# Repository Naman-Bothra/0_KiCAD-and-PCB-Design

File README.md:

# 0_KiCAD-and-PCB-Design
# Simple LED Driver Circuit

A foundational, low-power hardware design featuring a single-cell battery source, a current-limiting resistor, and a Light Emitting Diode (LED). This project serves as a clean baseline for schematic capture, electrical rule checking (ERC), custom footprint assignment, and manufacturing output generation using KiCad.

---

##  Project Overview

The objective of this project is to implement a robust, reliable, and mathematically sound LED indicator loop. LEDs are non-linear components with negligible internal resistance once their forward voltage threshold is crossed. To prevent over-current conditions and immediate component failure, this circuit incorporates a precisely calculated series resistor acting as a dedicated current limiter.

### Key Specifications
* **Supply Voltage ($V_{CC}$):** 3.0V DC (Optimized for standard CR2032 or dual AA/AAA battery configurations)
* **Target Forward Current ($I_f$):** ~10mA to 15mA (Balances ideal brightness with battery longevity)
* **Form Factor:** Minimalist PCB, routing single-sided or dual-layer copper tracks.

---

## 📊 Schematic & Circuit Design

The circuit is designed entirely within the **KiCad Schematic Editor**. The architecture utilizes explicit power distribution nets to decouple the power generation node from the functional loop.

### Component Breakdown
* **BT101 (Battery_Cell):** Direct current (DC) source providing system potential.
* **R101 (R_US):** Current-limiting resistor configured using the US-style schematic symbol.
* **D101 (LED):** Standard semiconductor diode indicator.
* **PWR_FLAG:** KiCad utility power flags appended to the `VCC` and `GND` nets to explicitly declare power-generating pins and successfully satisfy Electrical Rules Check (ERC) compilation.

### The Physics (Ohm's Law Calculation)
To ensure optimal current regulation, the resistor value was derived using the standard load equation:

$$R = \frac{V_{CC} - V_f}{I_f}$$

*Where $V_f$ represents the forward voltage drop characteristic of the selected LED substrate (typically 1.8V to 2.1V for standard red/green indicators).*

---

## 🎨 PCB Layout & Manufacturing Best Practices

The physical implementation of the layout adheres strictly to industry-standard DFM (Design for Manufacturability) guidelines:

---

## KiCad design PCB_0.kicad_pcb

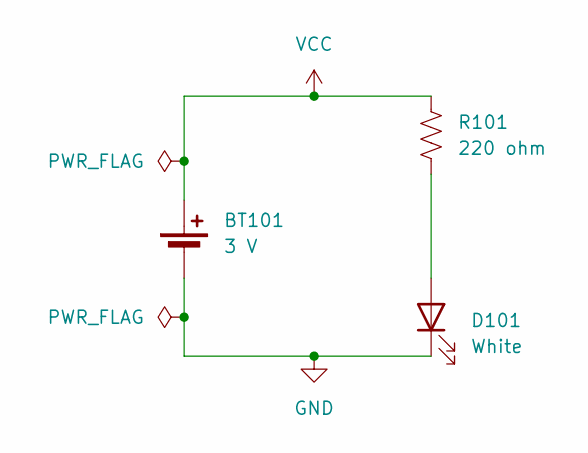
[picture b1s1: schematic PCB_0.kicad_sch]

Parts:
BT101: 3 V; BatteryHolder_Keystone_500
D101: White; LED_D3.0mm_Horizontal_O1.27mm_Z2.0mm_Clear
R101: 220 ohm; R_Axial_DIN0207_L6.3mm_D2.5mm_P2.54mm_Vertical

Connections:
GND: BT101.2 (-), D101.1 (K)
unnamed: D101.2 (A), R101.2
VCC: BT101.1 (+), R101.1

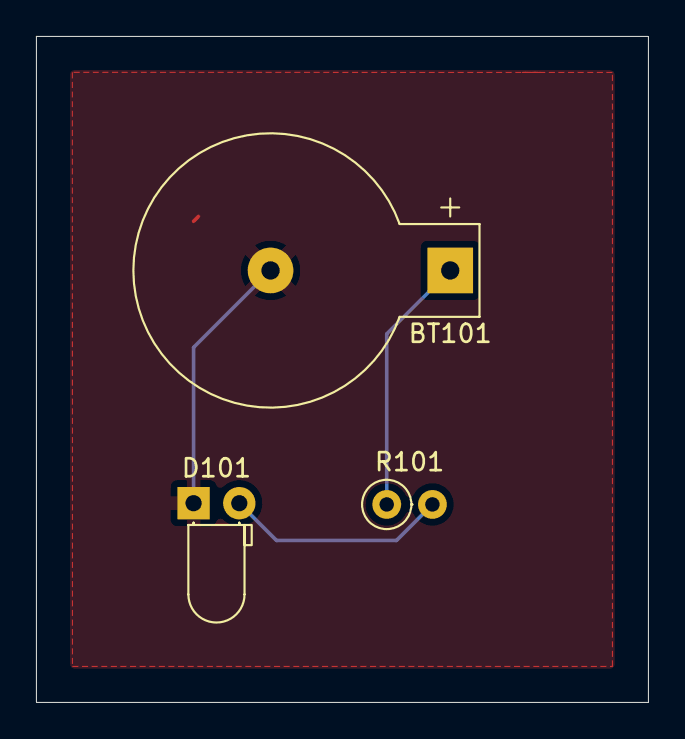
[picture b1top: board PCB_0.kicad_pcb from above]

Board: 2 copper layers, 34.0 x 37.0 mm, 3 parts (0 on the bottom side), 3 nets.

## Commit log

2026-06-19 0_KiCAD and PCB Design.md
